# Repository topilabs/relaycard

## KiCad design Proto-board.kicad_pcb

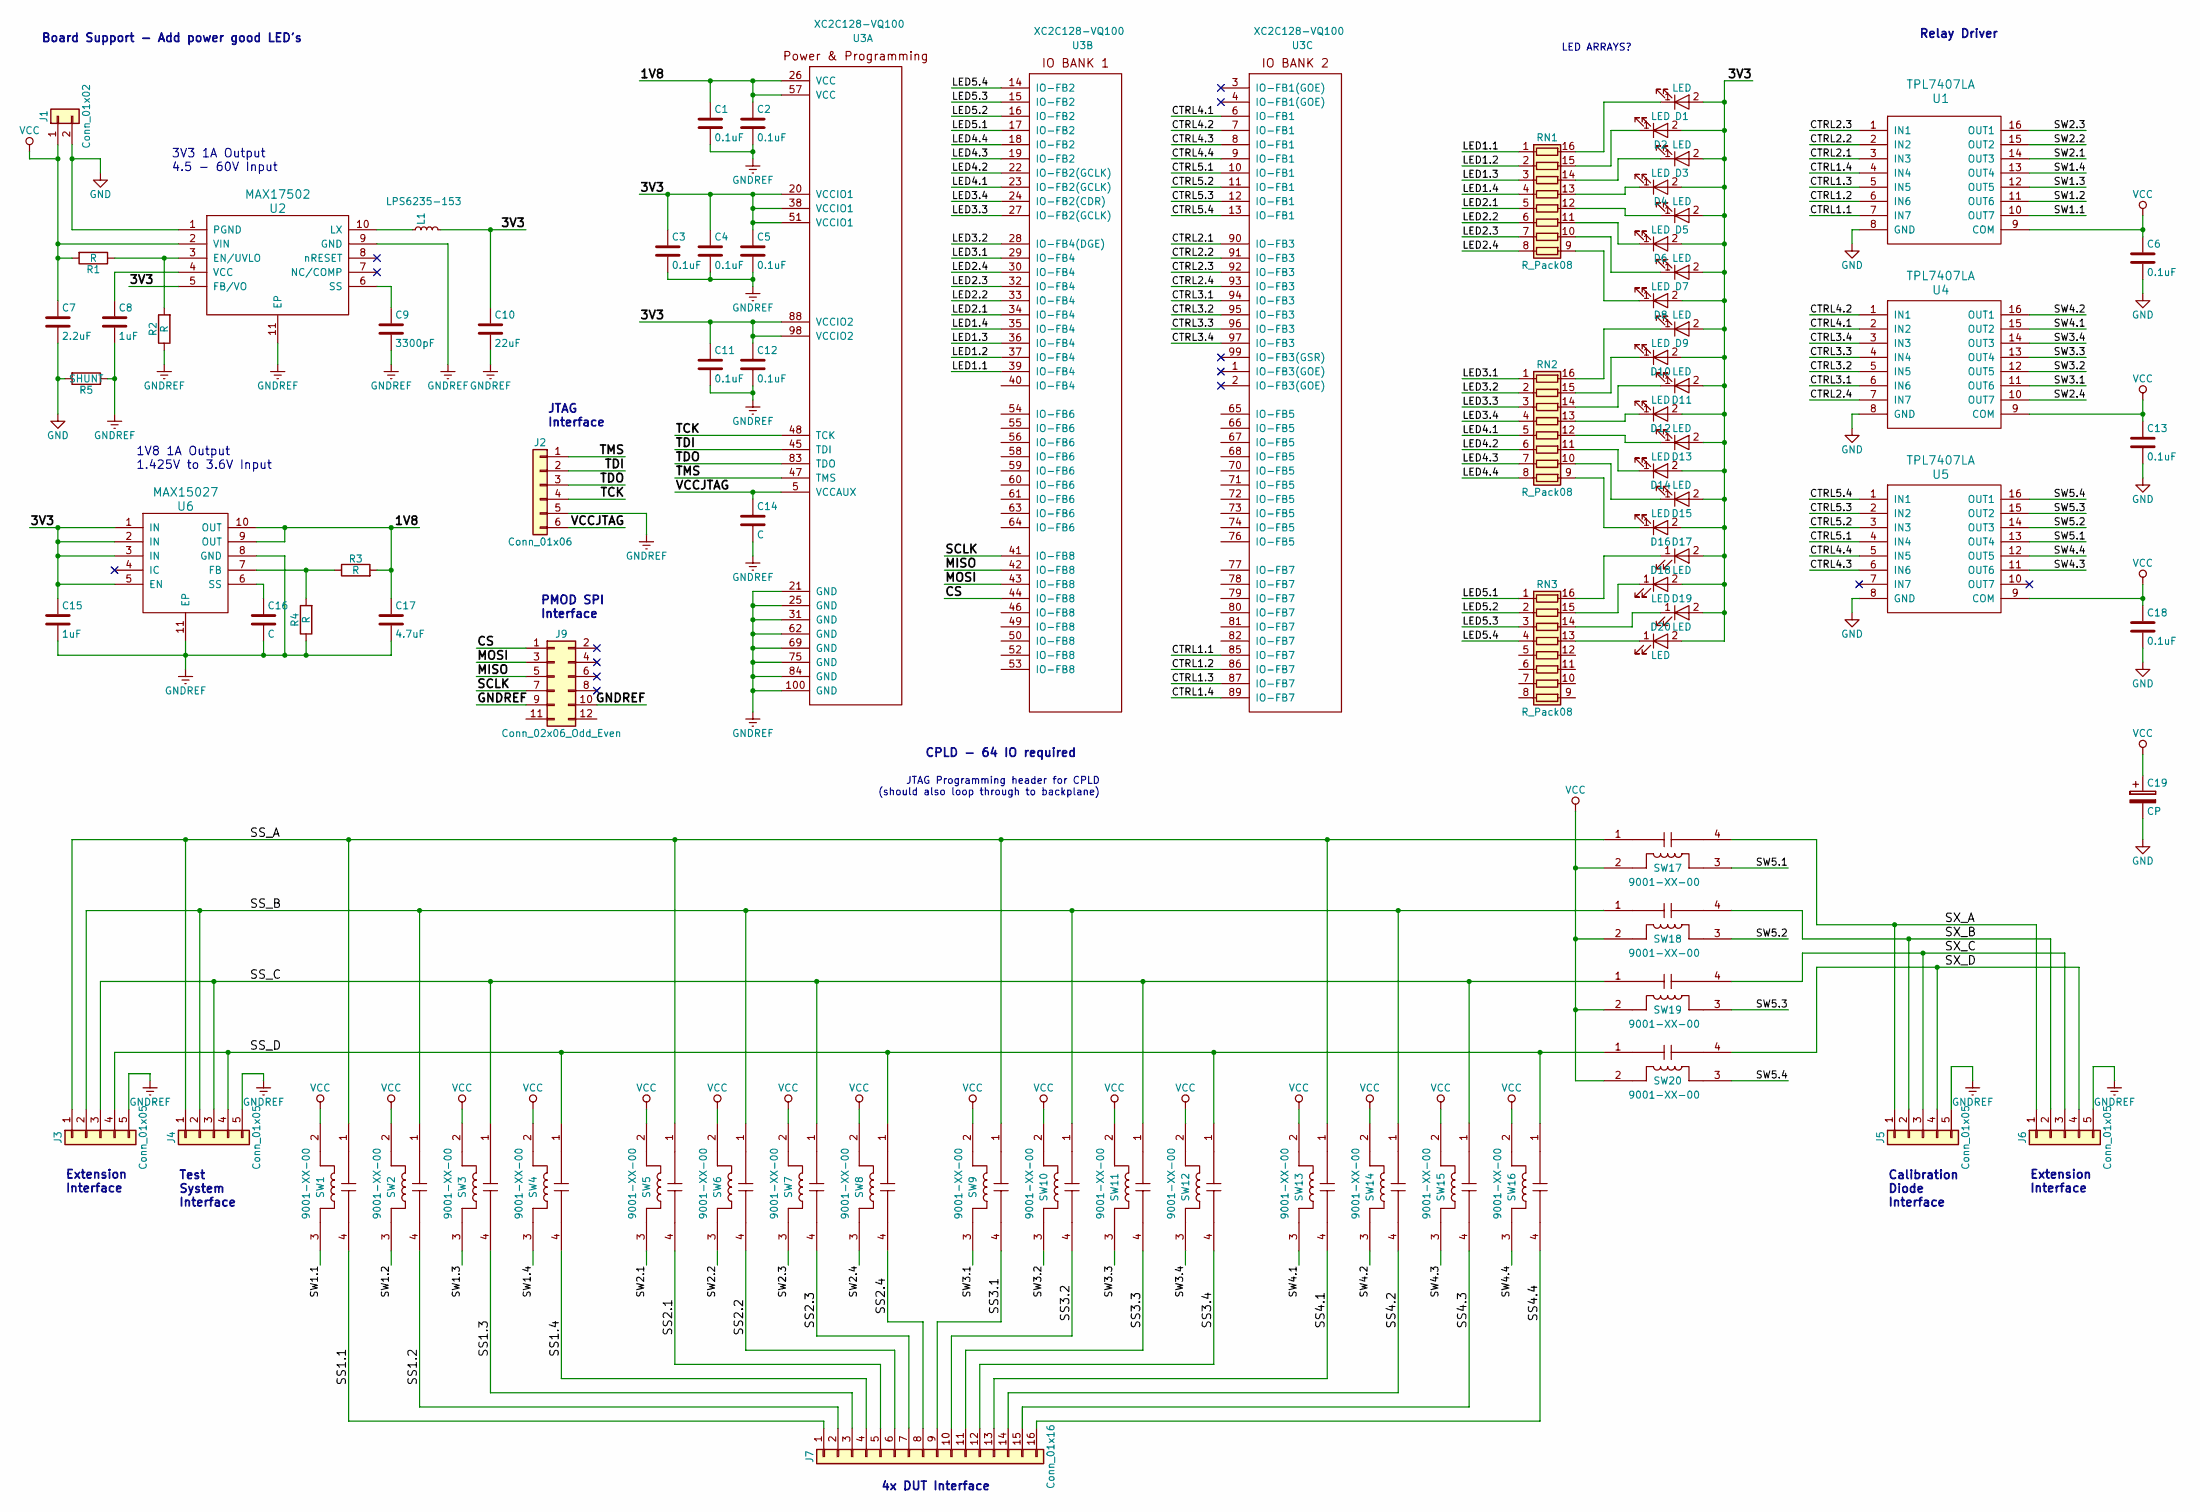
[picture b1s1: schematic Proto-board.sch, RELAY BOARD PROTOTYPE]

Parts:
C1, C2, C3, C4, C5, C6, C11, C12, C13, C18: 0.1uF; C_1206_HandSoldering
C7: 2.2uF; C_1210_HandSoldering
C8, C15: 1uF; C_1210_HandSoldering
C9: 3300pF; C_0603_HandSoldering
C10: 22uF; C_1210_HandSoldering
C14: C; C_1206_HandSoldering
C16: C; C_0603_HandSoldering
C17: 4.7uF; C_1210_HandSoldering
C19: CP; CP_Elec_8x5.4
D1, D2, D3, D4, D5, D6, D7, D8, D9, D10, D11, D12, D13, D14, D15, D16, D17, D18, D19, D20: LED; LED_0603_HandSoldering
J1: Conn_01x02; Pin_Header_Straight_1x02_Pitch2.54mm
J2: Conn_01x06; Pin_Header_Straight_1x06_Pitch2.54mm
J3, J4, J5, J6: Conn_01x05; Pin_Header_Straight_1x05_Pitch2.54mm
J7: Conn_01x16; Pin_Header_Straight_1x16_Pitch2.54mm
J9: Conn_02x06_Odd_Even; Pin_Header_Straight_2x06_Pitch2.54mm
L1: LPS6235-153; L_Coilcraft_XAL5030
R1, R2, R3, R4: R; R_1206_HandSoldering
R5: SHUNT; R_1206_HandSoldering
RN1, RN2, RN3: R_Pack08; SOIC-16
SW1, SW2, SW3, SW4, SW5, SW6, SW7, SW8, SW9, SW10, SW11, SW12, SW13, SW14, SW15, SW16, SW17, SW18, SW19, SW20: 9001-XX-00; SIP-4
U1, U4, U5: TPL7407LA; TSSOP-16_4.4x5mm_Pitch0.65mm
U2: MAX17502; DFN-10-1EP_3x3mm_Pitch0.5mm
U3: XC2C128-VQ100; TQFP-100_14x14mm_Pitch0.5mm
U6: MAX15027; DFN-10-1EP_3x3mm_Pitch0.5mm

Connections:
/1V8: C1.1, C2.1, C17.1, R3.2, U3.26 (VCC), U3.57 (VCC), U6.9 (OUT), U6.10 (OUT)
/3V3: C3.1, C4.1, C5.1, C10.1, C11.1, C12.1, C15.1, D1.2 (A), D2.2 (A), D3.2 (A), D4.2 (A), D5.2 (A), D6.2 (A), D7.2 (A), D8.2 (A), D9.2 (A), D10.2 (A), D11.2 (A), D12.2 (A), D13.2 (A), D14.2 (A), D15.2 (A), D16.2 (A), D17.2 (A), D18.2 (A), D19.2 (A), D20.2 (A), L1.2, U2.5 (FB/VO), U3.20 (VCCIO1), U3.38 (VCCIO1), U3.51 (VCCIO1), U3.88 (VCCIO2), U3.98 (VCCIO2), U6.1 (IN), U6.2 (IN), U6.3 (IN), U6.5 (EN)
/CS: J9.1, U3.44 (IO-FB8)
/CTRL1.1: U1.7 (IN7), U3.85 (IO-FB7)
/CTRL1.2: U1.6 (IN6), U3.86 (IO-FB7)
/CTRL1.3: U1.5 (IN5), U3.87 (IO-FB7)
/CTRL1.4: U1.4 (IN4), U3.89 (IO-FB7)
/CTRL2.1: U1.3 (IN3), U3.90 (IO-FB3)
/CTRL2.2: U1.2 (IN2), U3.91 (IO-FB3)
/CTRL2.3: U1.1 (IN1), U3.92 (IO-FB3)
/CTRL2.4: U3.93 (IO-FB3), U4.7 (IN7)
/CTRL3.1: U3.94 (IO-FB3), U4.6 (IN6)
/CTRL3.2: U3.95 (IO-FB3), U4.5 (IN5)
/CTRL3.3: U3.96 (IO-FB3), U4.4 (IN4)
/CTRL3.4: U3.97 (IO-FB3), U4.3 (IN3)
/CTRL4.1: U3.6 (IO-FB1), U4.2 (IN2)
/CTRL4.2: U3.7 (IO-FB1), U4.1 (IN1)
/CTRL4.3: U3.8 (IO-FB1), U5.6 (IN6)
/CTRL4.4: U3.9 (IO-FB1), U5.5 (IN5)
/CTRL5.1: U3.10 (IO-FB1), U5.4 (IN4)
/CTRL5.2: U3.11 (IO-FB1), U5.3 (IN3)
/CTRL5.3: U3.12 (IO-FB1), U5.2 (IN2)
/CTRL5.4: U3.13 (IO-FB1), U5.1 (IN1)
/LED1.1: RN1.1 (R1.1), U3.39 (IO-FB4)
/LED1.2: RN1.2 (R2.1), U3.37 (IO-FB4)
/LED1.3: RN1.3 (R3.1), U3.36 (IO-FB4)
/LED1.4: RN1.4 (R4.1), U3.35 (IO-FB4)
/LED2.1: RN1.5 (R5.1), U3.34 (IO-FB4)
/LED2.2: RN1.6 (R6.1), U3.33 (IO-FB4)
/LED2.3: RN1.7 (R7.1), U3.32 (IO-FB4)
/LED2.4: RN1.8 (R8.1), U3.30 (IO-FB4)
/LED3.1: RN2.1 (R1.1), U3.29 (IO-FB4)
/LED3.2: RN2.2 (R2.1), U3.28 (IO-FB4(DGE))
/LED3.3: RN2.3 (R3.1), U3.27 (IO-FB2(GCLK))
/LED3.4: RN2.4 (R4.1), U3.24 (IO-FB2(CDR))
/LED4.1: RN2.5 (R5.1), U3.23 (IO-FB2(GCLK))
/LED4.2: RN2.6 (R6.1), U3.22 (IO-FB2(GCLK))
/LED4.3: RN2.7 (R7.1), U3.19 (IO-FB2)
/LED4.4: RN2.8 (R8.1), U3.18 (IO-FB2)
/LED5.1: RN3.1 (R1.1), U3.17 (IO-FB2)
/LED5.2: RN3.2 (R2.1), U3.16 (IO-FB2)
/LED5.3: RN3.3 (R3.1), U3.15 (IO-FB2)
/LED5.4: RN3.4 (R4.1), U3.14 (IO-FB2)
/MISO: J9.5, U3.42 (IO-FB8)
/MOSI: J9.3, U3.43 (IO-FB8)
/SCLK: J9.7, U3.41 (IO-FB8)
/SS1.1: J7.1, SW1.4
/SS1.2: J7.2, SW2.4
/SS1.3: J7.3, SW3.4
/SS1.4: J7.4, SW4.4
/SS2.1: J7.5, SW5.4
/SS2.2: J7.6, SW6.4
/SS2.3: J7.7, SW7.4
/SS2.4: J7.8, SW8.4
/SS3.1: J7.9, SW9.4
/SS3.2: J7.10, SW10.4
/SS3.3: J7.11, SW11.4
/SS3.4: J7.12, SW12.4
/SS4.1: J7.13, SW13.4
/SS4.2: J7.14, SW14.4
/SS4.3: J7.15, SW15.4
/SS4.4: J7.16, SW16.4
/SS_A: J3.1, J4.1, SW1.1, SW5.1, SW9.1, SW13.1, SW17.1
/SS_B: J3.2, J4.2, SW2.1, SW6.1, SW10.1, SW14.1, SW18.1
/SS_C: J3.3, J4.3, SW3.1, SW7.1, SW11.1, SW15.1, SW19.1
/SS_D: J3.4, J4.4, SW4.1, SW8.1, SW12.1, SW16.1, SW20.1
/SW1.1: SW1.3, U1.10 (OUT7)
/SW1.2: SW2.3, U1.11 (OUT6)
/SW1.3: SW3.3, U1.12 (OUT5)
/SW1.4: SW4.3, U1.13 (OUT4)
/SW2.1: SW5.3, U1.14 (OUT3)
/SW2.2: SW6.3, U1.15 (OUT2)
/SW2.3: SW7.3, U1.16 (OUT1)
/SW2.4: SW8.3, U4.10 (OUT7)
/SW3.1: SW9.3, U4.11 (OUT6)
/SW3.2: SW10.3, U4.12 (OUT5)
/SW3.3: SW11.3, U4.13 (OUT4)
/SW3.4: SW12.3, U4.14 (OUT3)
/SW4.1: SW13.3, U4.15 (OUT2)
/SW4.2: SW14.3, U4.16 (OUT1)
/SW4.3: SW15.3, U5.11 (OUT6)
/SW4.4: SW16.3, U5.12 (OUT5)
/SW5.1: SW17.3, U5.13 (OUT4)
/SW5.2: SW18.3, U5.14 (OUT3)
/SW5.3: SW19.3, U5.15 (OUT2)
/SW5.4: SW20.3, U5.16 (OUT1)
/SX_A: J5.1, J6.1, SW17.4
/SX_B: J5.2, J6.2, SW18.4
/SX_C: J5.3, J6.3, SW19.4
/SX_D: J5.4, J6.4, SW20.4
/TCK: J2.4, U3.48 (TCK)
/TDI: J2.2, U3.45 (TDI)
/TDO: J2.3, U3.83 (TDO)
/TMS: J2.1, U3.47 (TMS)
/VCCJTAG: C14.1, J2.6, U3.5 (VCCAUX)
GND: C6.2, C7.2, C13.2, C18.2, C19.2, J1.2, R5.2, U1.8 (GND), U2.1 (PGND), U4.8 (GND), U5.8 (GND)
GNDREF: C1.2, C2.2, C3.2, C4.2, C5.2, C8.2, C9.2, C10.2, C11.2, C12.2, C14.2, C15.2, C16.2, C17.2, J2.5, J3.5, J4.5, J5.5, J6.5, J9.9, J9.10, R2.1, R4.1, R5.1, U2.9 (GND), U2.11 (EP), U3.21 (GND), U3.25 (GND), U3.31 (GND), U3.62 (GND), U3.69 (GND), U3.75 (GND), U3.84 (GND), U3.100 (GND), U6.8 (GND), U6.11 (EP)
unnamed: C8.1, U2.4 (VCC)
unnamed: C9.1, U2.6 (SS)
unnamed: C16.1, U6.6 (SS)
unnamed: D1.1 (K), RN1.16 (R1.2)
unnamed: D2.1 (K), RN1.15 (R2.2)
unnamed: D3.1 (K), RN1.14 (R3.2)
unnamed: D4.1 (K), RN1.13 (R4.2)
unnamed: D5.1 (K), RN1.12 (R5.2)
unnamed: D6.1 (K), RN1.11 (R6.2)
unnamed: D7.1 (K), RN1.10 (R7.2)
unnamed: D8.1 (K), RN1.9 (R8.2)
unnamed: D9.1 (K), RN2.16 (R1.2)
unnamed: D10.1 (K), RN2.15 (R2.2)
unnamed: D11.1 (K), RN2.14 (R3.2)
unnamed: D12.1 (K), RN2.13 (R4.2)
unnamed: D13.1 (K), RN2.12 (R5.2)
unnamed: D14.1 (K), RN2.11 (R6.2)
unnamed: D15.1 (K), RN2.10 (R7.2)
unnamed: D16.1 (K), RN2.9 (R8.2)
unnamed: D17.1 (K), RN3.16 (R1.2)
unnamed: D18.1 (K), RN3.15 (R2.2)
unnamed: D19.1 (K), RN3.14 (R3.2)
unnamed: D20.1 (K), RN3.13 (R4.2)
unnamed: L1.1, U2.10 (LX)
unnamed: R1.1, R2.2, U2.3 (EN/UVLO)
unnamed: R3.1, R4.2, U6.7 (FB)
VCC: C6.1, C7.1, C13.1, C18.1, C19.1, J1.1, R1.2, SW1.2, SW2.2, SW3.2, SW4.2, SW5.2, SW6.2, SW7.2, SW8.2, SW9.2, SW10.2, SW11.2, SW12.2, SW13.2, SW14.2, SW15.2, SW16.2, SW17.2, SW18.2, SW19.2, SW20.2, U1.9 (COM), U2.2 (VIN), U4.9 (COM), U5.9 (COM)

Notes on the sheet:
Board Support - Add power good LED's
CPLD - 64 IO required
Relay Driver
JTAG Programming header for CPLD (should also loop through to backplane)
LED ARRAYS?
Calibration Diode Interface
Extension Interface
Test System Interface
4x DUT Interface
3V3 1A Output 4.5 - 60V Input
1V8 1A Output 1.425V to 3.6V Input
JTAG Interface
PMOD SPI Interface

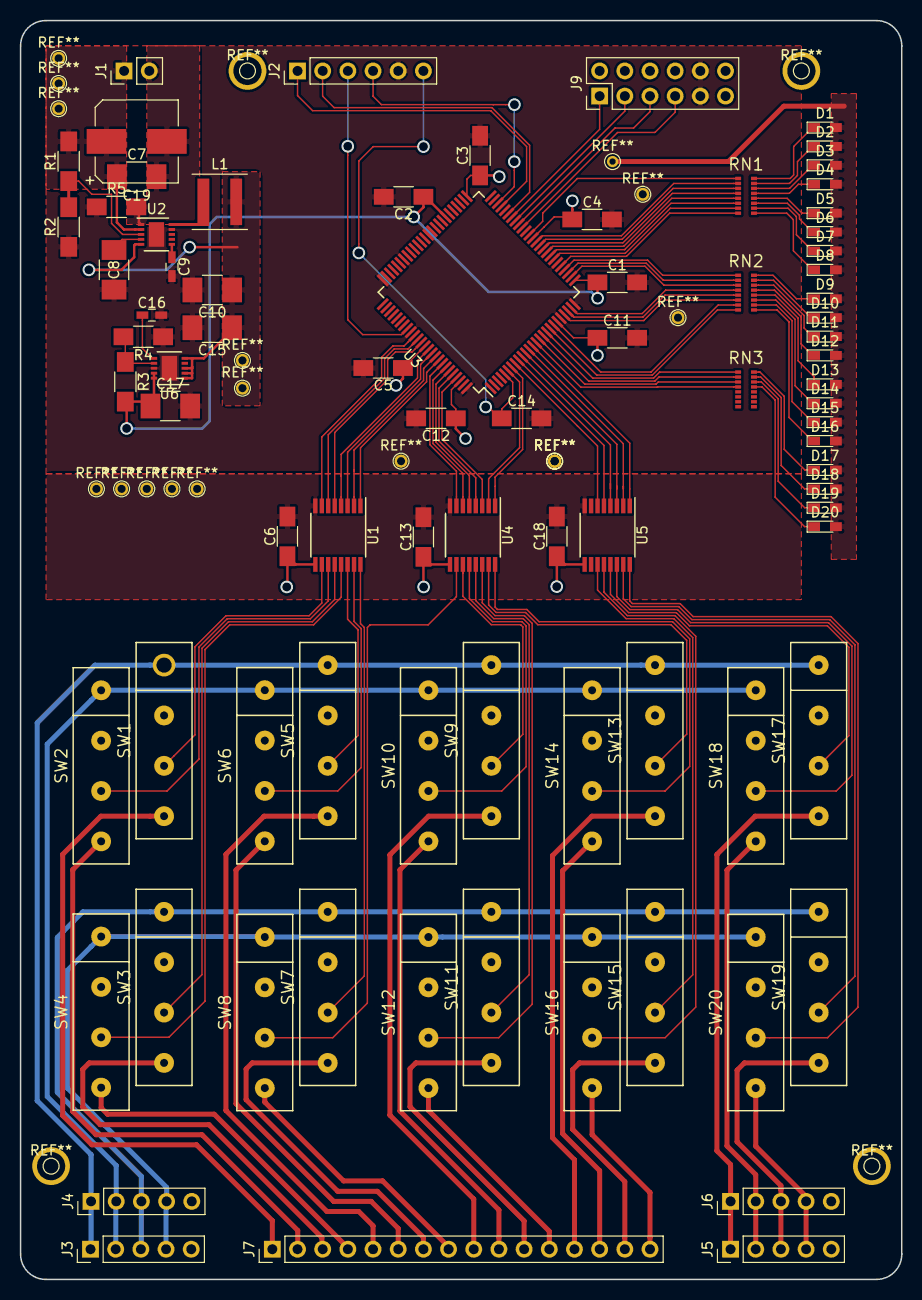
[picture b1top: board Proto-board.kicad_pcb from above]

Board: 2 copper layers, 88.9 x 127.0 mm, 82 parts (0 on the bottom side), 124 nets.

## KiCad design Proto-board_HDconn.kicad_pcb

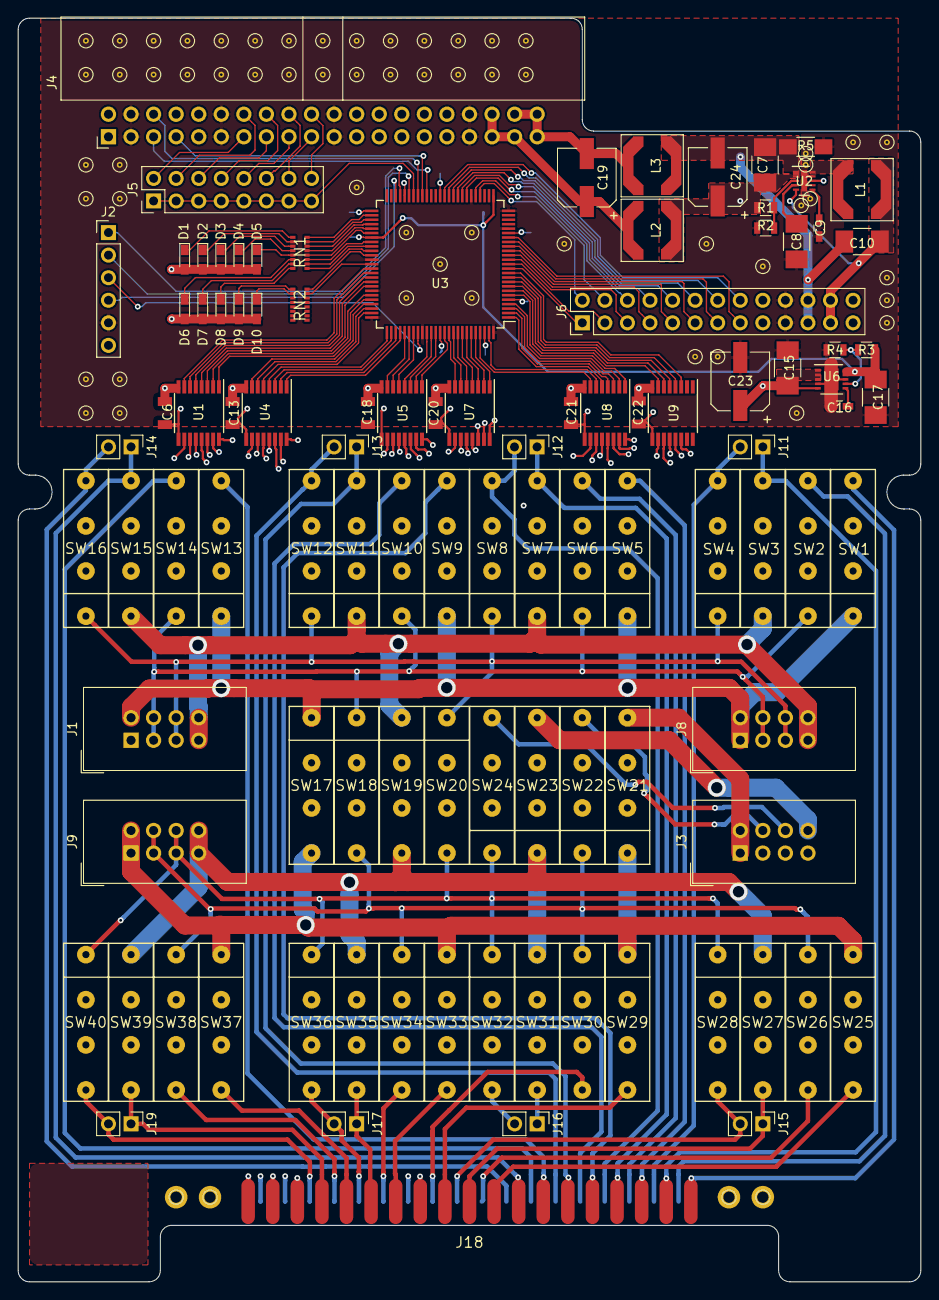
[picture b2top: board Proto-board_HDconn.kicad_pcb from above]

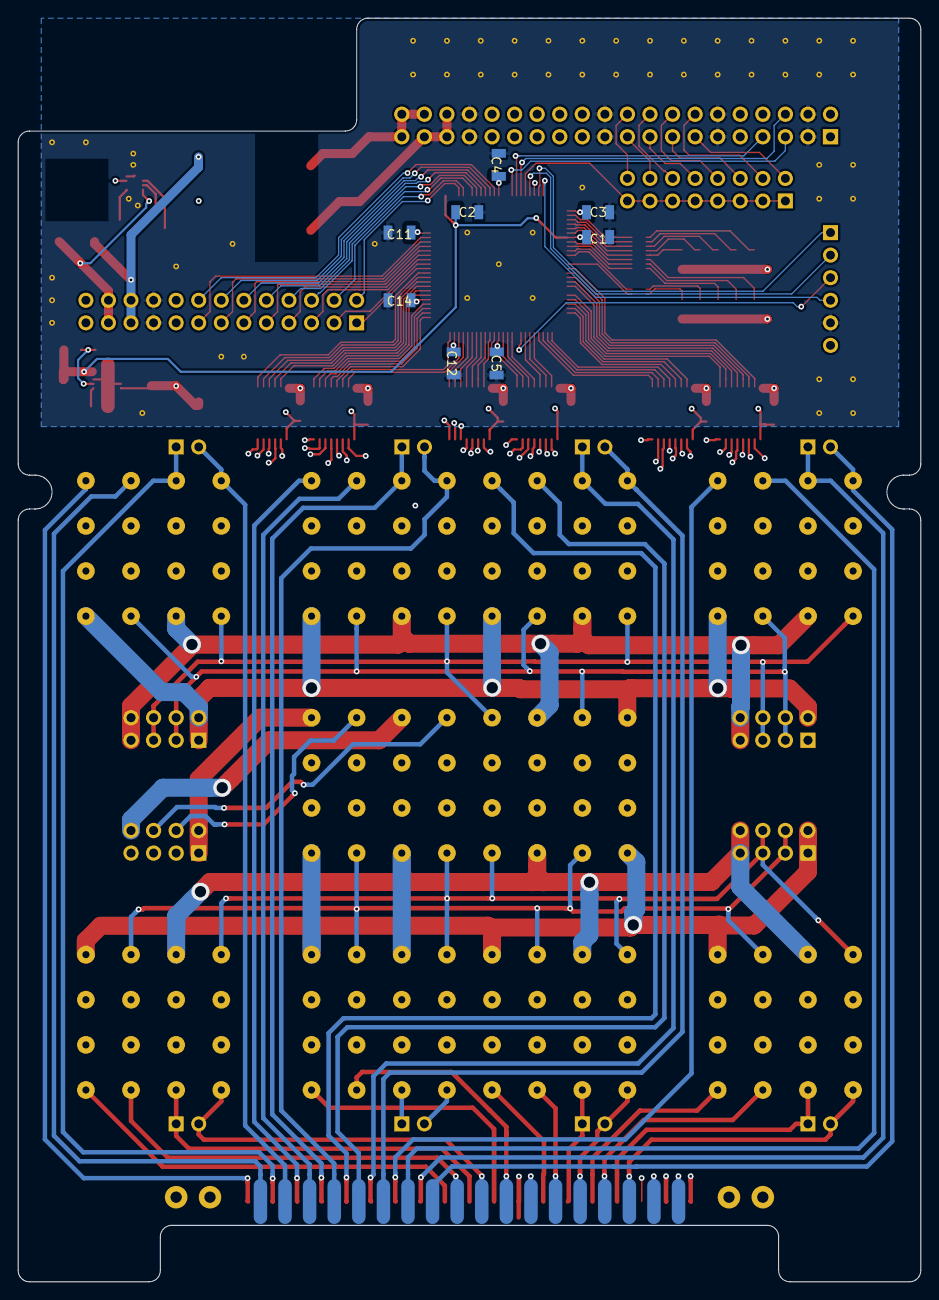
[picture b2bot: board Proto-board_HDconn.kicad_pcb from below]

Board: 4 copper layers, 101.6 x 142.2 mm, 110 parts (8 on the bottom side), 191 nets.

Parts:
C1, C2, C3, C4, C5, C6, C11, C12, C13, C18, C20, C21, C22: 0.1uF; 1206_PROTO
C7: 2.2uF; C_1210_HandSoldering
C8, C15: 1uF; C_1210_HandSoldering
C9: 3300pF; C_0603_HandSoldering
C10: 22uF; C_1210_HandSoldering
C14: C; 1206_PROTO
C16: C; C_0603_HandSoldering
C17: 4.7uF; C_1210_HandSoldering
C19, C23, C24: CP; CP_Elec_6.3x4.5
D1, D2, D3, D4, D5, D6, D7, D8, D9, D10: LED; LED_0603_HandSoldering
J1, J3, J8, J9: Conn_01x08; IDC-Header_2x04_Pitch2.54mm_Straight
J2: Conn_01x06; Pin_Header_Straight_1x06_Pitch2.54mm
J4: Conn_02x20_Odd_Even; IDC-Header_2x20_Pitch2.54mm_Angled
J5: Conn_02x08_Odd_Even; Pin_Header_Straight_2x08_Pitch2.54mm
J6: Conn_02x13_Odd_Even; Pin_Header_Straight_2x13_Pitch2.54mm
J11, J12, J13, J14, J15, J16, J17, J19: Conn_01x02; Pin_Header_Straight_1x02_Pitch2.54mm
J18: DB37_Female; DC37_F_Straddle
L1, L2, L3: LPS6235-153; LPS6235
R1, R2, R3, R4: R; R_0805
R5: SHUNT; R_1206_HandSoldering
RN1, RN2: R_Pack08; SOIC-16
SW1, SW2, SW3, SW4, SW5, SW6, SW7, SW8, SW9, SW10, SW11, SW12, SW13, SW14, SW15, SW16, SW17, SW18, SW19, SW20, SW21, SW22, SW23, SW24, SW25, SW26, SW27, SW28, SW29, SW30, SW31, SW32, SW33, SW34, SW35, SW36, SW37, SW38, SW39, SW40: 9001-XX-00; SIP-4
U1, U4, U5, U7, U8, U9: TPL7407LA; TSSOP-16_4.4x5mm_Pitch0.65mm
U2: MAX17502G; DFN-10-1EP_2x3mm_Pitch0.5mm
U3: XC2C128-VQ100; TQFP-100_14x14mm_Pitch0.5mm
U6: MAX15027; DFN-10-1EP_3x3mm_Pitch0.5mm

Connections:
/1V8: C1.1, C2.1, C17.1, R3.2, U3.26, U3.57, U6.9, U6.10
/3V3: C3.1, C4.1, C5.1, C11.1, C12.1, C14.1, C15.1, C23.1, D1.2, D2.2, D3.2, D4.2, D5.2, D6.2, D7.2, D8.2, D9.2, D10.2, J2.6, J4.31, J4.32, J6.17, J6.18, U3.5, U3.20, U3.38, U3.51, U3.88, U3.98, U6.1, U6.2, U6.3, U6.5
/24+: C7.1, C24.1, J6.25, J6.26, L2.2, R1.2, U2.2
/24+S: C19.1, J4.35, J4.36, J4.37, L2.1
/24-S: C19.2, J4.38, J4.39, J4.40, L3.1
/A1ASNS: J11.2, J18.21, SW4.4
/A1ASRC: J11.1, J18.2, SW3.4
/A1BSNS: J15.2, J18.29, SW28.4
/A1BSRC: J15.1, J18.10, SW27.4
/A2ASNS: J12.2, J18.23, SW8.4
/A2ASRC: J12.1, J18.4, SW7.4
/A2BSNS: J16.2, J18.31, SW32.4
/A2BSRC: J16.1, J18.12, SW31.4
/A3ASNS: J13.2, J18.25, SW12.4
/A3ASRC: J13.1, J18.6, SW11.4
/A3BSNS: J17.2, J18.33, SW36.4
/A3BSRC: J17.1, J18.14, SW35.4
/A4ASNS: J14.2, J18.27, SW16.4
/A4ASRC: J14.1, J18.8, SW15.4
/A4BSNS: J18.35, J19.2, SW40.4
/A4BSRC: J18.16, J19.1, SW39.4
/AASNS: J1.5, J1.6, J8.5, J8.6, SW4.1, SW8.1, SW12.1, SW16.1, SW20.1
/AASRC: J1.7, J1.8, J8.7, J8.8, SW3.1, SW7.1, SW11.1, SW15.1, SW19.1
/ABSNS: J9.5, J9.6, SW20.4, SW24.1, SW28.1, SW32.1, SW36.1, SW40.1
/ABSRC: J9.7, J9.8, SW19.4, SW23.1, SW27.1, SW31.1, SW35.1, SW39.1
/APDSNS: J3.5, J3.6, J18.19, SW24.4
/APDSRC: J3.7, J3.8, J18.37, SW23.4
/C1ASNS: J18.20, SW2.4
/C1ASRC: J18.1, SW1.4
/C1BSNS: J18.28, SW26.4
/C1BSRC: J18.9, SW25.4
/C2ASNS: J18.22, SW6.4
/C2ASRC: J18.3, SW5.4
/C2BSNS: J18.30, SW30.4
/C2BSRC: J18.11, SW29.4
/C3ASNS: J18.24, SW10.4
/C3ASRC: J18.5, SW9.4
/C3BSNS: J18.32, SW34.4
/C3BSRC: J18.13, SW33.4
/C4ASNS: J18.26, SW14.4
/C4ASRC: J18.7, SW13.4
/C4BSNS: J18.34, SW38.4
/C4BSRC: J18.15, SW37.4
/CASNS: J1.3, J1.4, J8.3, J8.4, SW2.1, SW6.1, SW10.1, SW14.1, SW18.1
/CASRC: J1.1, J1.2, J8.1, J8.2, SW1.1, SW5.1, SW9.1, SW13.1, SW17.1
/CBSNS: J9.3, J9.4, SW18.4, SW22.1, SW26.1, SW30.1, SW34.1, SW38.1
/CBSRC: J9.1, J9.2, SW17.4, SW21.1, SW25.1, SW29.1, SW33.1, SW37.1
/CPDSNS: J3.3, J3.4, J18.18, SW22.4
/CPDSRC: J3.1, J3.2, J18.36, SW21.4
/CS: J5.1, J5.3, J5.5, J5.7, J5.9, J5.11, J5.13, J5.15, U3.44
/CS0: J4.13, J5.2
/CS1: J4.14, J5.4
/CS2: J4.15, J5.6
/CS3: J4.16, J5.8
/CS4: J4.17, J5.10
/CS5: J4.18, J5.12
/CS6: J4.19, J5.14
/CS7: J4.20, J5.16
/CTRL1: U3.11, U9.3
/CTRL2: U3.10, U9.4
/CTRL3: U3.9, U9.5
/CTRL4: U3.8, U9.6
/CTRL5: U3.2, U8.4
/CTRL6: U3.97, U8.7
/CTRL7: U3.94, U7.3
/CTRL8: U3.91, U7.6
/CTRL9: U3.87, U5.2
/CTRL10: U3.82, U5.5
/CTRL11: U3.79, U4.1
/CTRL12: U3.76, U4.4
/CTRL13: U1.2, U3.70
/CTRL14: U1.3, U3.68
/CTRL15: U1.5, U3.66
/CTRL16: U1.7, U3.64
/CTRL17: U3.74, U4.5
/CTRL18: U3.78, U4.2
/CTRL19: U3.81, U5.6
/CTRL20: U3.86, U5.3
/CTRL21: U3.1, U8.5
/CTRL22: U3.96, U7.1
/CTRL23: U3.93, U7.4
/CTRL24: U3.90, U7.7
/CTRL25: U3.7, U9.7
/CTRL26: U3.6, U8.1
/CTRL27: U3.4, U8.2
/CTRL28: U3.3, U8.3
/CTRL29: U3.99, U8.6
/CTRL30: U3.95, U7.2
/CTRL31: U3.92, U7.5
/CTRL32: U3.89, U5.1
/CTRL33: U3.85, U5.4
/CTRL34: U3.80, U5.7
/CTRL35: U3.77, U4.3
/CTRL36: U3.73, U4.6
/CTRL37: U3.72, U4.7
/CTRL38: U1.1, U3.71
/CTRL39: U1.4, U3.67
/CTRL40: U1.6, U3.65
/ENABLE0: J6.2, U3.29
/ENABLE1: J6.4, U3.30
/ENABLE2: J6.6, U3.32
/ENABLE3: J6.8, U3.33
/ENABLE4: J6.10, U3.34
/ENABLE5: J6.12, U3.35
/ENABLE6: J6.14, U3.36
/ENABLE7: J6.16, U3.37
/HOLD0: J6.1, U3.12
/HOLD1: J6.3, U3.13
/HOLD2: J6.5, U3.14
/HOLD3: J6.7, U3.15
/HOLD4: J6.9, U3.16
/HOLD5: J6.11, U3.17
/HOLD6: J6.13, U3.18
/HOLD7: J6.15, U3.19
/LED1.1: RN1.8, U3.52
/LED1.2: RN1.7, U3.53
/LED1.3: RN1.6, U3.54
/LED1.4: RN1.5, U3.55
/LED2.1: RN1.4, U3.56
/LED2.2: RN1.3, U3.58
/LED2.3: RN1.2, U3.59
/LED2.4: RN1.1, U3.60
/LED3.1: RN2.8, U3.61
/LED3.2: RN2.7, U3.63
/MISO0: J4.7, U3.42
/MOSI0: J4.6, U3.43
/SCLK0: J4.5, U3.41
/SW1: SW1.3, U9.14
/SW2: SW2.3, U9.13
/SW3: SW3.3, U9.12
/SW4: SW4.3, U9.11
/SW5: SW5.3, U8.13
/SW6: SW6.3, U8.10
/SW7: SW7.3, U7.14
/SW8: SW8.3, U7.11
/SW9: SW9.3, U5.15
/SW10: SW10.3, U5.12
/SW11: SW11.3, U4.16
/SW12: SW12.3, U4.13
/SW13: SW13.3, U1.15
/SW14: SW14.3, U1.14
/SW15: SW15.3, U1.12
/SW16: SW16.3, U1.10
/SW17: SW17.3, U4.12
/SW18: SW18.3, U4.15
/SW19: SW19.3, U5.11
/SW20: SW20.3, U5.14
/SW21: SW21.3, U8.12
/SW22: SW22.3, U7.16
/SW23: SW23.3, U7.13
/SW24: SW24.3, U7.10
/SW25: SW25.3, U9.10
/SW26: SW26.3, U8.16
/SW27: SW27.3, U8.15
/SW28: SW28.3, U8.14
/SW29: SW29.3, U8.11
/SW30: SW30.3, U7.15
/SW31: SW31.3, U7.12
/SW32: SW32.3, U5.16
/SW33: SW33.3, U5.13
/SW34: SW34.3, U5.10
/SW35: SW35.3, U4.14
/SW36: SW36.3, U4.11
/SW37: SW37.3, U4.10
/SW38: SW38.3, U1.16
/SW39: SW39.3, U1.13
/SW40: SW40.3, U1.11
/TCK: J2.4, U3.48
/TDI: J2.2, U3.45
/TDO: J2.3, U3.83
/TMS: J2.1, U3.47
/vccgood: U2.8, U3.46
GND: C6.2, C7.2, C10.2, C13.2, C18.2, C20.2, C21.2, C22.2, C24.2, J6.21, J6.22, L3.2, R5.2, U1.8, U2.1, U4.8, U5.8, U7.8, U8.8, U9.8
GNDREF: C1.2, C2.2, C3.2, C4.2, C5.2, C8.2, C9.2, C11.2, C12.2, C14.2, C15.2, C16.2, C17.2, C23.2, J2.5, J4.3, J4.4, J4.11, J4.12, J4.21, J4.22, J4.33, J4.34, J6.19, J6.20, R2.1, R4.1, R5.1, U2.9, U2.11, U3.21, U3.25, U3.31, U3.62, U3.69, U3.75, U3.84, U3.100, U6.4, U6.8, U6.11
unnamed: C8.1, U2.4
unnamed: C9.1, U2.6
unnamed: C16.1, U6.6
unnamed: D1.1, RN1.9
unnamed: D2.1, RN1.10
unnamed: D3.1, RN1.11
unnamed: D4.1, RN1.12
unnamed: D5.1, RN1.13
unnamed: D6.1, RN1.14
unnamed: D7.1, RN1.15
unnamed: D8.1, RN1.16
unnamed: D9.1, RN2.9
unnamed: D10.1, RN2.10
unnamed: L1.1, U2.10
unnamed: R1.1, R2.2, U2.3
unnamed: R3.1, R4.2, U6.7
VCC: C6.1, C10.1, C13.1, C18.1, C20.1, C21.1, C22.1, J6.23, J6.24, L1.2, SW1.2, SW2.2, SW3.2, SW4.2, SW5.2, SW6.2, SW7.2, SW8.2, SW9.2, SW10.2, SW11.2, SW12.2, SW13.2, SW14.2, SW15.2, SW16.2, SW17.2, SW18.2, SW19.2, SW20.2, SW21.2, SW22.2, SW23.2, SW24.2, SW25.2, SW26.2, SW27.2, SW28.2, SW29.2, SW30.2, SW31.2, SW32.2, SW33.2, SW34.2, SW35.2, SW36.2, SW37.2, SW38.2, SW39.2, SW40.2, U1.9, U2.5, U4.9, U5.9, U7.9, U8.9, U9.9

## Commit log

2018-05-02 HDConn V01, the first fabbed PCB's
2018-06-11 Final version of protoboard prior to major revision.
2018-06-19 Second version (4x6 card) revC, which was ordered.
2018-06-20 Version submitted for PCB mfg.
2018-07-31 First commit to shared repo after board fab and bring-up of 10 boards.
